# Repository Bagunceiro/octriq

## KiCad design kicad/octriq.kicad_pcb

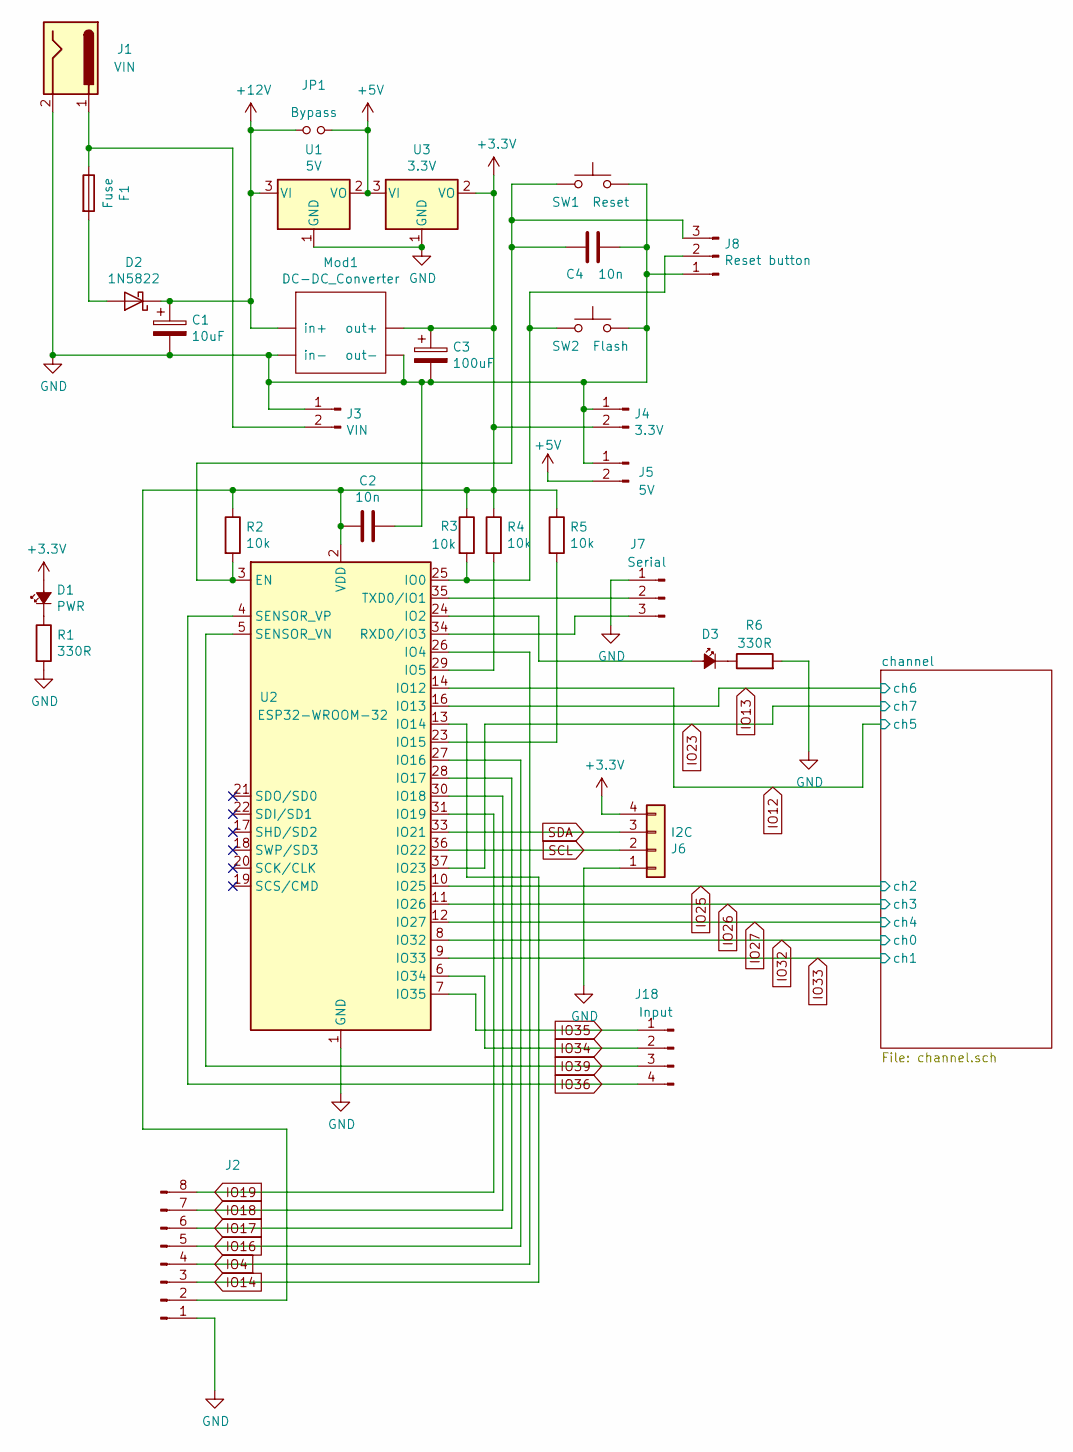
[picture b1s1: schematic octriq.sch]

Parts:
C1: 10uF; CP_Radial_D12.5mm_P7.50mm+pins
C2, C4: 10n; C_0805_2012Metric_Pad1.15x1.40mm_HandSolder
C3: 100uF; CP_Radial_D12.5mm_P7.50mm+pins
D1: PWR; LED_0805_2012Metric_Pad1.15x1.40mm_HandSolder
D2: 1N5822; D_DO-201AD_P5.08mm_Vertical_AnodeUp
D3: BUILT-IN; LED_0805_2012Metric_Pad1.15x1.40mm_HandSolder
F1: Fuse; R_Axial_DIN0411_L9.9mm_D3.6mm_P15.24mm_Horizontal
J1: VIN; BarrelJack_Horizontal
J2: Conn_01x06_Male; PinHeader_3x06_P2.54mm_Vertical
J3: VIN; PinHeader_1x02_P2.54mm_Vertical
J4: 3.3V; PinHeader_1x02_P2.54mm_Vertical
J5: 5V; PinHeader_1x02_P2.54mm_Vertical
J6: I2C; PinHeader_1x04_P2.54mm_Vertical
J7: Serial; PinHeader_1x03_P2.54mm_Vertical
J8: Reset button; PinHeader_1x03_P2.54mm_Vertical
J18: Input; PinHeader_1x04_P2.54mm_Vertical
JP1: Bypass; SolderJumper-2_P1.3mm_Open_TrianglePad1.0x1.5mm
Mod1: DC-DC_Converter; small_Buck
R1, R6: 330R; R_0805_2012Metric_Pad1.15x1.40mm_HandSolder
R2, R3, R4, R5: 10k; R_0805_2012Metric_Pad1.15x1.40mm_HandSolder
SW1: Reset; SW_PUSH_6mm
SW2: Flash; SW_PUSH_6mm
U1: 5V; SOT-223-3_TabPin2
U2: ESP32-WROOM-32
U3: 3.3V; SOT-223-3_TabPin2

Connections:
+3V3: C2.2, C3.1, D1.2 (A), J2.2, J4.2, J6.4, Mod1.2 (out+), R2.1, R3.1, R4.1, R5.1, U2.2 (VDD), U3.2 (VO)
+5V: J5.2, JP1.2, U1.2 (VO), U3.3 (VI)
+12V: C1.1, D2.1 (K), JP1.1, Mod1.1 (in+), U1.3 (VI); also elsewhere on the board
GND: C1.2, C2.1, C3.2, C4.1, J1.2, J2.1, J3.1, J4.1, J5.1, J6.1, J7.1, J8.1, Mod1.3 (out-), Mod1.4 (in-), R1.2, R6.2, SW1.2, SW2.2, U1.1 (GND), U2.1 (GND), U2.15 (GND), U2.38 (GND), U2.39 (GND), U3.1 (GND); also elsewhere on the board
IO4: J2.4, U2.26 (IO4)
IO12: U2.14 (IO12); also elsewhere on the board
IO13: U2.16 (IO13); also elsewhere on the board
IO14: J2.3, U2.13 (IO14)
IO16: J2.5, U2.27 (IO16)
IO17: J2.6, U2.28 (IO17)
IO18: J2.7, U2.30 (IO18)
IO19: J2.8, U2.31 (IO19)
IO23: U2.37 (IO23); also elsewhere on the board
IO25: U2.10 (IO25); also elsewhere on the board
IO26: U2.11 (IO26); also elsewhere on the board
IO27: U2.12 (IO27); also elsewhere on the board
IO32: U2.8 (IO32); also elsewhere on the board
IO33: U2.9 (IO33); also elsewhere on the board
IO34: J18.2, U2.6 (IO34)
IO35: J18.1, U2.7 (IO35)
IO36: J18.4, U2.4 (SENSOR_VP)
IO39: J18.3, U2.5 (SENSOR_VN)
unnamed: C4.2, J8.3, R2.2, SW1.1, U2.3 (EN)
unnamed: D1.1 (K), R1.1
unnamed: D2.2 (A), F1.2
unnamed: D3.1 (K), R6.1
unnamed: D3.2 (A), U2.24 (IO2)
unnamed: F1.1, J1.1, J3.2
unnamed: J7.2, U2.35 (TXD0/IO1)
unnamed: J7.3, U2.34 (RXD0/IO3)
unnamed: J8.2, R3.2, SW2.1, U2.25 (IO0)
unnamed: R4.2, U2.29 (IO5)
unnamed: R5.2, U2.23 (IO15)
SCL: J6.2, U2.36 (IO22)
SDA: J6.3, U2.33 (IO21)

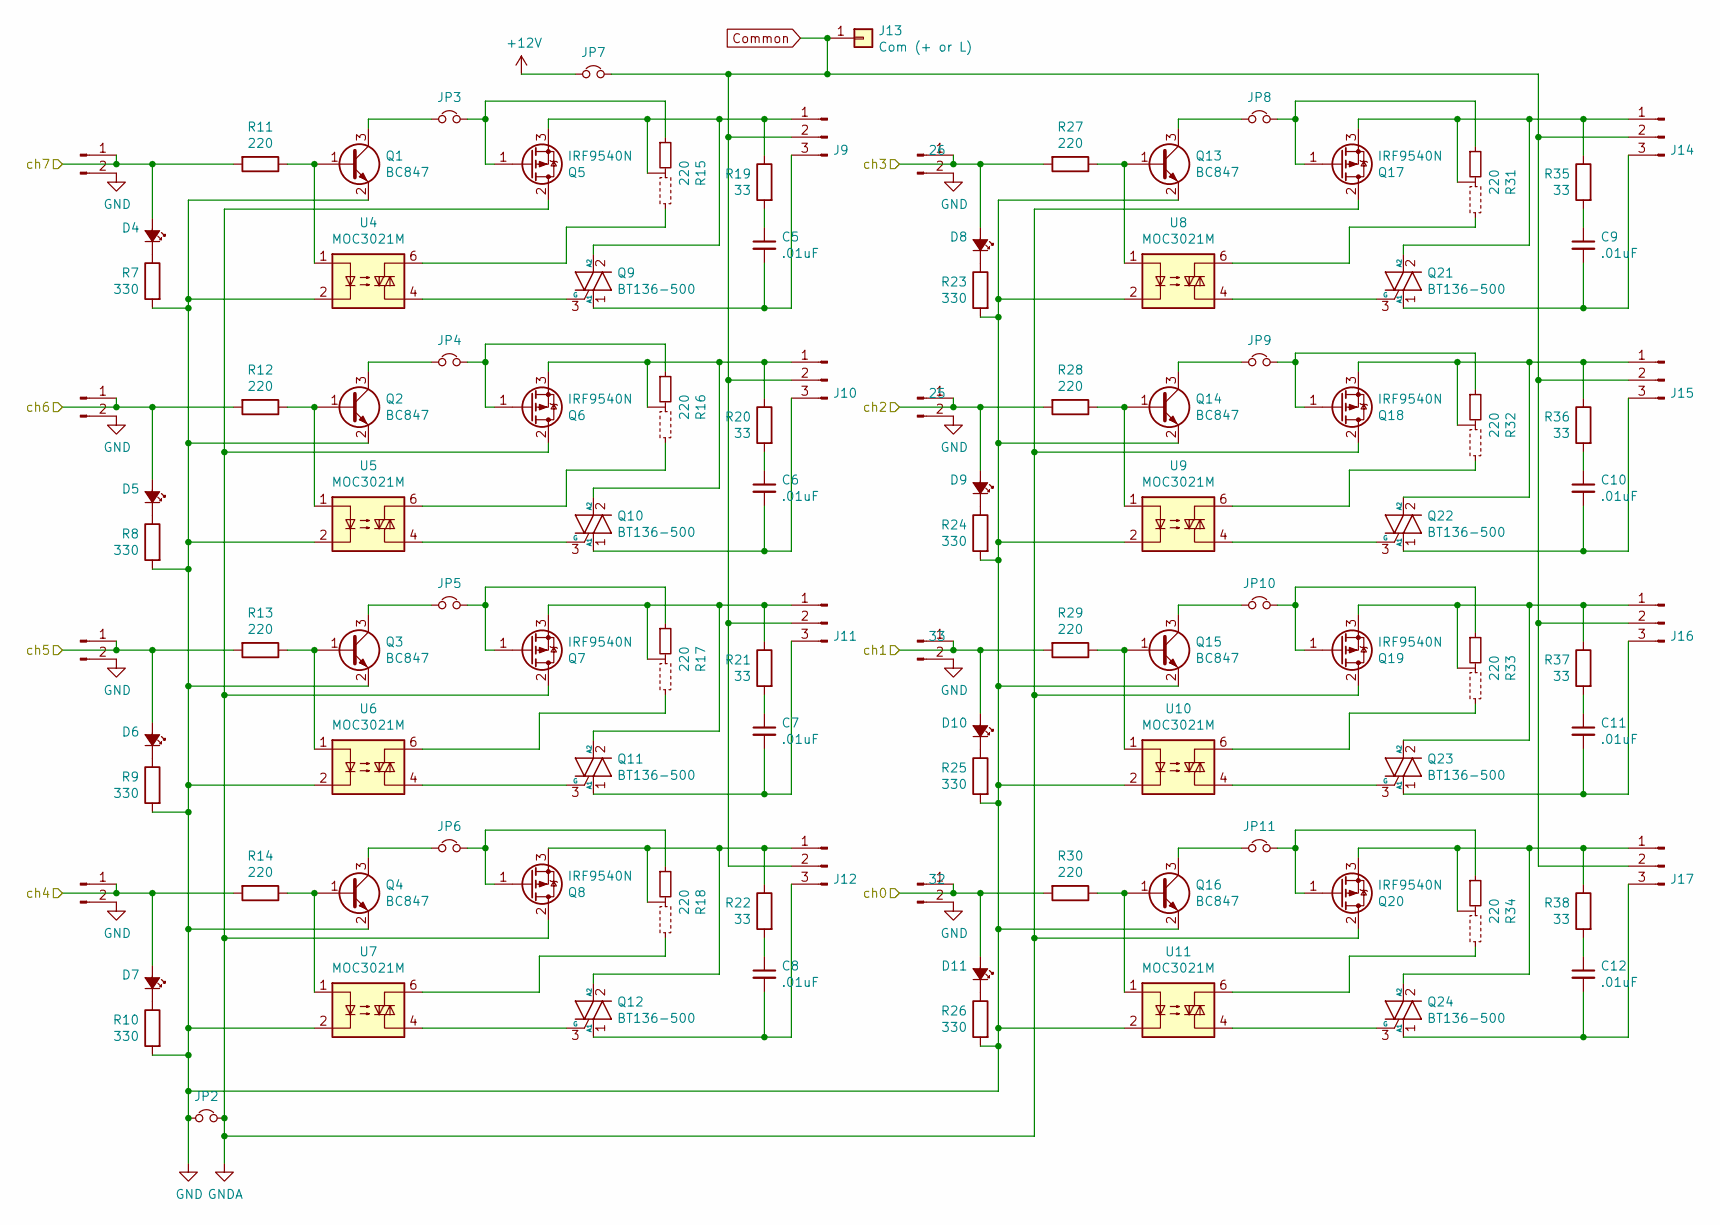
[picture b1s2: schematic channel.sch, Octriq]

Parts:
C5, C6, C7, C8, C9, C10, C11, C12: .01uF; C_0805_2012Metric_Pad1.15x1.40mm_HandSolder
D4, D5, D6, D7, D8, D9, D10, D11: LED_Small_ALT; LED_0805_2012Metric_Pad1.15x1.40mm_HandSolder
J9, J10, J11, J12, J14, J15, J16, J17: Conn_01x03_Male; Molex_KK+Born2
J13: Com (+ or L); Spade_Terminal
JP2, JP3, JP4, JP5, JP6, JP7, JP8, JP9, JP10, JP11: Jumper_NC_Small; wide_jumper
Q1, Q2, Q3, Q4, Q13, Q14, Q15, Q16: BC847; SOT-23
Q5, Q6, Q7, Q8, Q17, Q18, Q19, Q20: IRF9540N; TO-220-3_Vertical
Q9, Q10, Q11, Q12, Q21, Q22, Q23, Q24: BT136-500; TO-220-3_Vertical
R7, R8, R9, R10, R23, R24, R25, R26: 330; R_0805_2012Metric_Pad1.15x1.40mm_HandSolder
R11, R12, R13, R14, R27, R28, R29, R30: 220; R_0805_2012Metric_Pad1.15x1.40mm_HandSolder
R15, R16, R17, R18, R31, R32, R33, R34: 220; Resistor_0805_option
R19, R20, R21, R22, R35, R36, R37, R38: 33; R_0805_2012Metric_Pad1.15x1.40mm_HandSolder
TP1: 13; PinHeader_1x02_P2.54mm_Vertical
TP2: 12; PinHeader_1x02_P2.54mm_Vertical
TP3: 14; PinHeader_1x02_P2.54mm_Vertical
TP4: 27; PinHeader_1x02_P2.54mm_Vertical
TP5: 26; PinHeader_1x02_P2.54mm_Vertical
TP6: 25; PinHeader_1x02_P2.54mm_Vertical
TP7: 33; PinHeader_1x02_P2.54mm_Vertical
TP8: 32; PinHeader_1x02_P2.54mm_Vertical
U4, U5, U6, U7, U8, U9, U10, U11: MOC3021M; DIP-6_W7.62mm_Socket

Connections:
+12V: JP7.1; also elsewhere on the board
Common: J9.2, J10.2, J11.2, J12.2, J13.1, J14.2, J15.2, J16.2, J17.2, JP7.2
GND: JP2.1, Q1.2 (E), Q2.2 (E), Q3.2 (E), Q4.2 (E), Q13.2 (E), Q14.2 (E), Q15.2 (E), Q16.2 (E), R7.2, R8.2, R9.2, R10.2, R23.2, R24.2, R25.2, R26.2, TP1.2, TP2.2, TP3.2, TP4.2, TP5.2, TP6.2, TP7.2, TP8.2, U4.2, U5.2, U6.2, U7.2, U8.2, U9.2, U10.2, U11.2; also elsewhere on the board
GNDA: JP2.2, Q5.2 (D), Q6.2 (D), Q7.2 (D), Q8.2 (D), Q17.2 (D), Q18.2 (D), Q19.2 (D), Q20.2 (D)
IO12: D6.2 (A), R13.2, TP3.1; also elsewhere on the board
IO13: D5.2 (A), R12.2, TP2.1; also elsewhere on the board
IO23: D4.2 (A), R11.2, TP1.1; also elsewhere on the board
IO25: D9.2 (A), R28.2, TP6.1; also elsewhere on the board
IO26: D8.2 (A), R27.2, TP5.1; also elsewhere on the board
IO27: D7.2 (A), R14.2, TP4.1; also elsewhere on the board
IO32: D11.2 (A), R30.2, TP8.1; also elsewhere on the board
IO33: D10.2 (A), R29.2, TP7.1; also elsewhere on the board
unnamed: C5.1, R19.2
unnamed: C5.2, J9.3, Q9.1 (A1)
unnamed: C6.1, R20.2
unnamed: C6.2, J10.3, Q10.1 (A1)
unnamed: C7.1, R21.2
unnamed: C7.2, J11.3, Q11.1 (A1)
unnamed: C8.1, R22.2
unnamed: C8.2, J12.3, Q12.1 (A1)
unnamed: C9.1, R35.2
unnamed: C9.2, J14.3, Q21.1 (A1)
unnamed: C10.1, R36.2
unnamed: C10.2, J15.3, Q22.1 (A1)
unnamed: C11.1, R37.2
unnamed: C11.2, J16.3, Q23.1 (A1)
unnamed: C12.1, R38.2
unnamed: C12.2, J17.3, Q24.1 (A1)
unnamed: D4.1 (K), R7.1
unnamed: D5.1 (K), R8.1
unnamed: D6.1 (K), R9.1
unnamed: D7.1 (K), R10.1
unnamed: D8.1 (K), R23.1
unnamed: D9.1 (K), R24.1
unnamed: D10.1 (K), R25.1
unnamed: D11.1 (K), R26.1
unnamed: J9.1, Q5.3 (S), Q9.2 (A2), R15.1 (Common), R19.1
unnamed: J10.1, Q6.3 (S), Q10.2 (A2), R16.1 (Common), R20.1
unnamed: J11.1, Q7.3 (S), Q11.2 (A2), R17.1 (Common), R21.1
unnamed: J12.1, Q8.3 (S), Q12.2 (A2), R18.1 (Common), R22.1
unnamed: J14.1, Q17.3 (S), Q21.2 (A2), R31.1 (Common), R35.1
unnamed: J15.1, Q18.3 (S), Q22.2 (A2), R32.1 (Common), R36.1
unnamed: J16.1, Q19.3 (S), Q23.2 (A2), R33.1 (Common), R37.1
unnamed: J17.1, Q20.3 (S), Q24.2 (A2), R34.1 (Common), R38.1
unnamed: JP3.1, Q1.3 (C)
unnamed: JP3.2, Q5.1 (G), R15.2
unnamed: JP4.1, Q2.3 (C)
unnamed: JP4.2, Q6.1 (G), R16.2
unnamed: JP5.1, Q3.3 (C)
unnamed: JP5.2, Q7.1 (G), R17.2
unnamed: JP6.1, Q4.3 (C)
unnamed: JP6.2, Q8.1 (G), R18.2
unnamed: JP8.1, Q13.3 (C)
unnamed: JP8.2, Q17.1 (G), R31.2
unnamed: JP9.1, Q14.3 (C)
unnamed: JP9.2, Q18.1 (G), R32.2
unnamed: JP10.1, Q15.3 (C)
unnamed: JP10.2, Q19.1 (G), R33.2
unnamed: JP11.1, Q16.3 (C)
unnamed: JP11.2, Q20.1 (G), R34.2
unnamed: Q1.1 (B), R11.1, U4.1
unnamed: Q2.1 (B), R12.1, U5.1
unnamed: Q3.1 (B), R13.1, U6.1
unnamed: Q4.1 (B), R14.1, U7.1
unnamed: Q9.3 (G), U4.4
unnamed: Q10.3 (G), U5.4
unnamed: Q11.3 (G), U6.4
unnamed: Q12.3 (G), U7.4
unnamed: Q13.1 (B), R27.1, U8.1
unnamed: Q14.1 (B), R28.1, U9.1
unnamed: Q15.1 (B), R29.1, U10.1
unnamed: Q16.1 (B), R30.1, U11.1
unnamed: Q21.3 (G), U8.4
unnamed: Q22.3 (G), U9.4
unnamed: Q23.3 (G), U10.4
unnamed: Q24.3 (G), U11.4
unnamed: R15.3, U4.6
unnamed: R16.3, U5.6
unnamed: R17.3, U6.6
unnamed: R18.3, U7.6
unnamed: R31.3, U8.6
unnamed: R32.3, U9.6
unnamed: R33.3, U10.6
unnamed: R34.3, U11.6

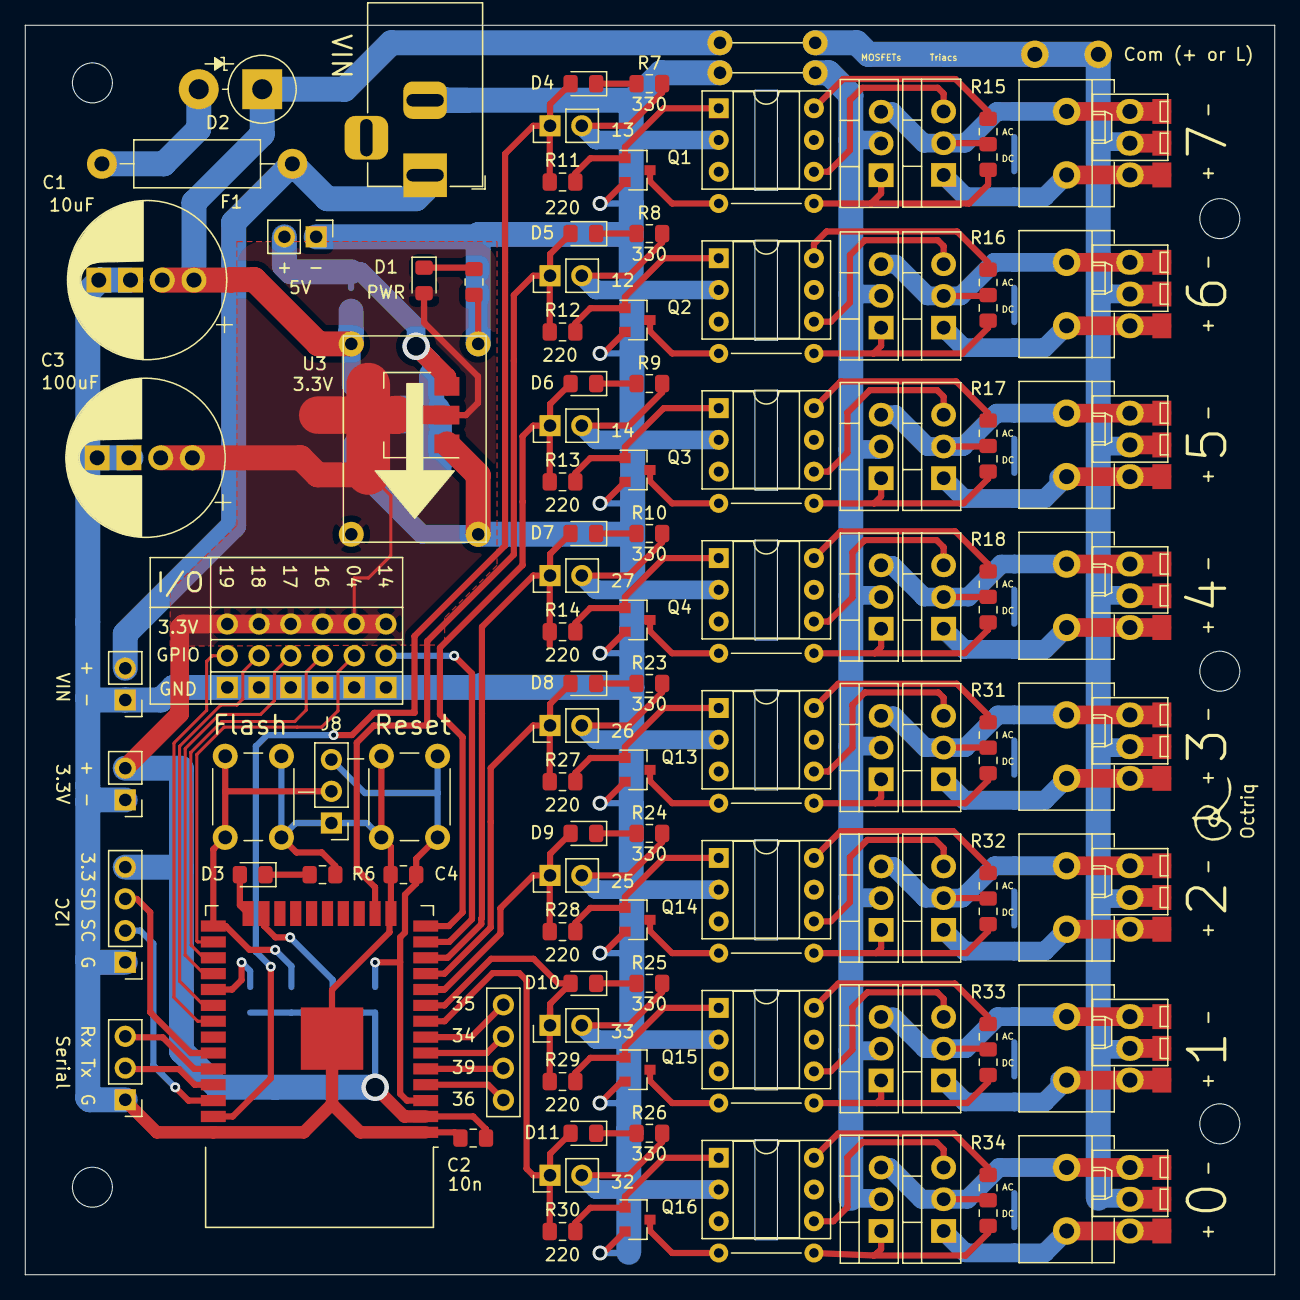
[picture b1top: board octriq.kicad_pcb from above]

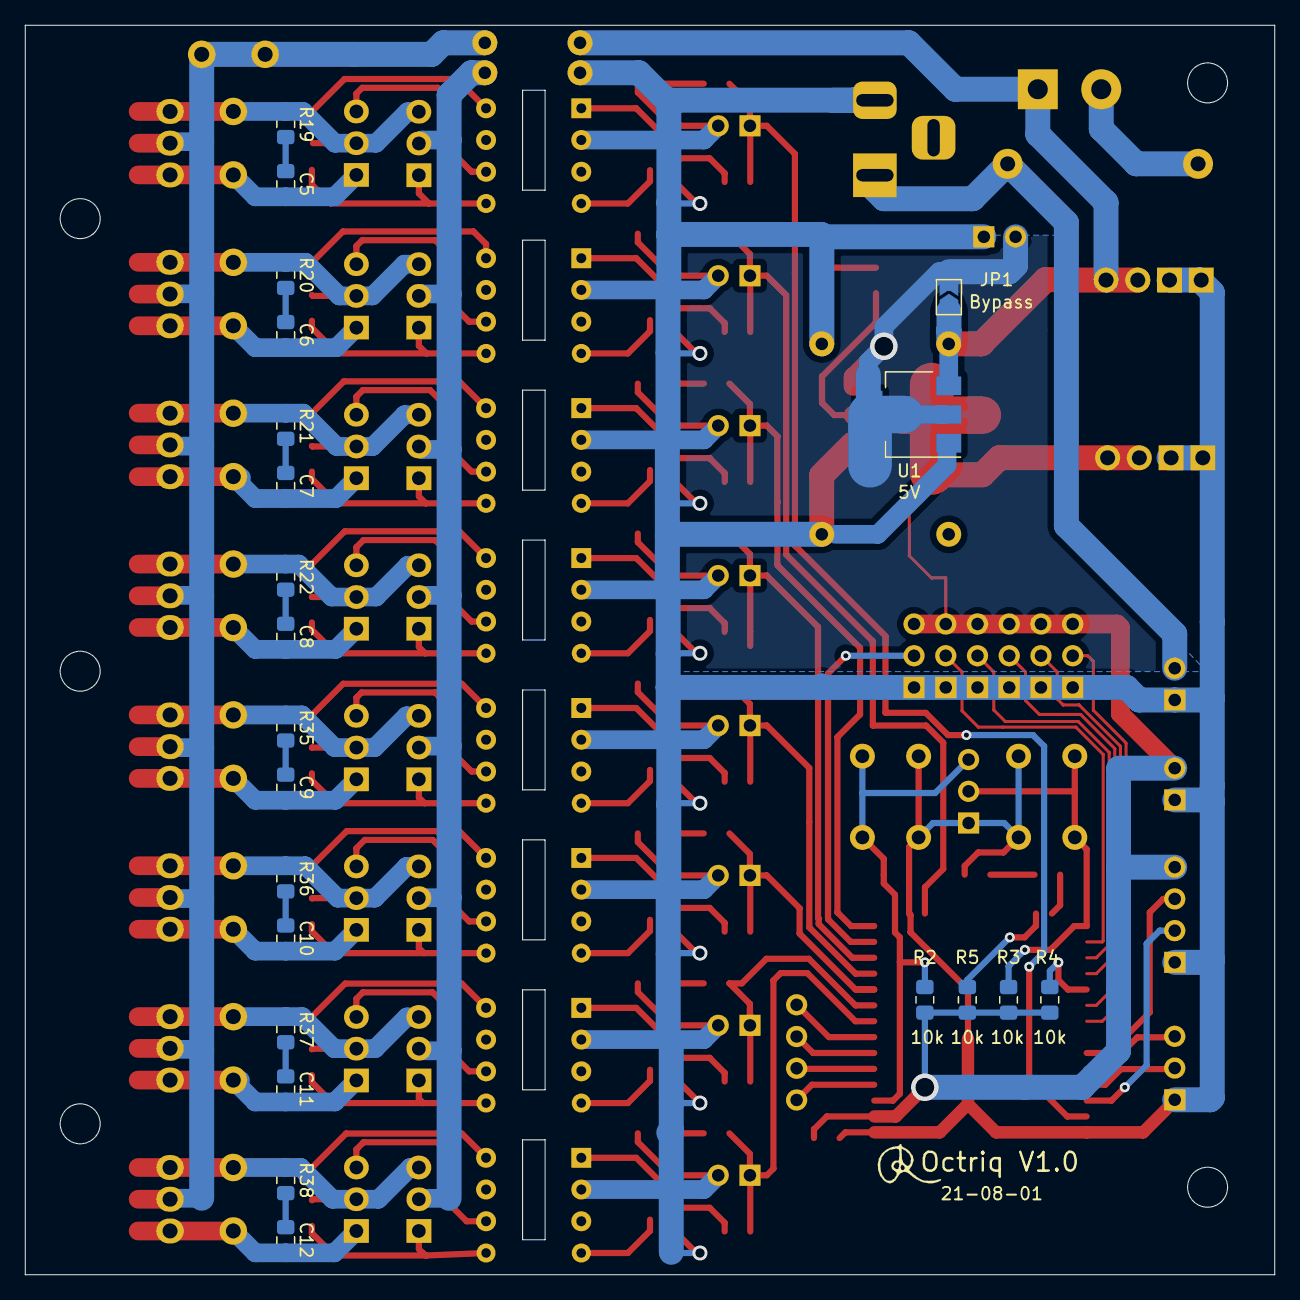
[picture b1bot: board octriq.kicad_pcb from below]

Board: 2 copper layers, 100.0 x 100.0 mm, 137 parts (22 on the bottom side), 109 nets.

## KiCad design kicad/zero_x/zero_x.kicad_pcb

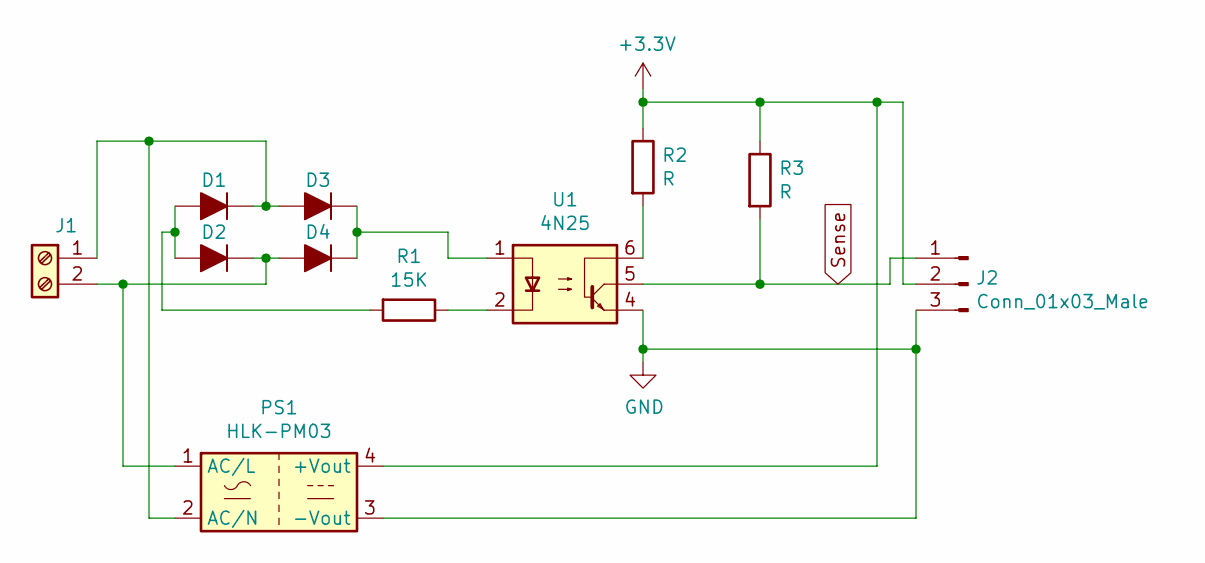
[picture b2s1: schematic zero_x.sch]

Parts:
D1, D2, D3, D4: D_ALT; D_A-405_P7.62mm_Horizontal
J1: Screw_Terminal_01x02; TerminalBlock_bornier-2_P5.08mm
J2: Conn_01x03_Male; PinHeader_1x03_P2.54mm_Vertical
PS1: HLK-PM03; Converter_ACDC_HiLink_HLK-PMxx
R1: 15K; R_Axial_DIN0617_L17.0mm_D6.0mm_P7.62mm_Vertical
R2, R3: R; R_Axial_DIN0207_L6.3mm_D2.5mm_P7.62mm_Horizontal
U1: 4N25; DIP-6_W7.62mm

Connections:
+3V3: J2.2, PS1.4 (+Vout), R2.1, R3.1
GND: J2.3, PS1.3 (-Vout), U1.4
unnamed: D1.1 (K), D3.2 (A), J1.1, PS1.2 (AC/N)
unnamed: D1.2 (A), D2.2 (A), R1.2
unnamed: D2.1 (K), D4.2 (A), J1.2, PS1.1 (AC/L)
unnamed: D3.1 (K), D4.1 (K), U1.1
unnamed: R1.1, U1.2
unnamed: R2.2, U1.6
Sense: J2.1, R3.2, U1.5

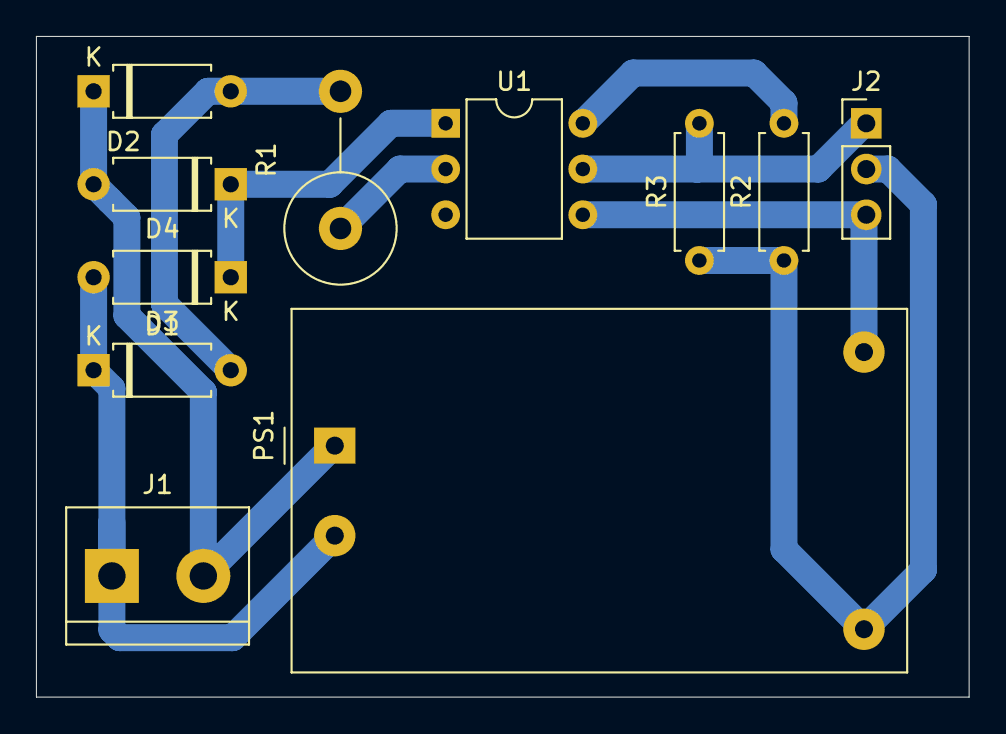
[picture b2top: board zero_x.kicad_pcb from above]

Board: 2 copper layers, 51.8 x 36.7 mm, 11 parts (0 on the bottom side), 9 nets.

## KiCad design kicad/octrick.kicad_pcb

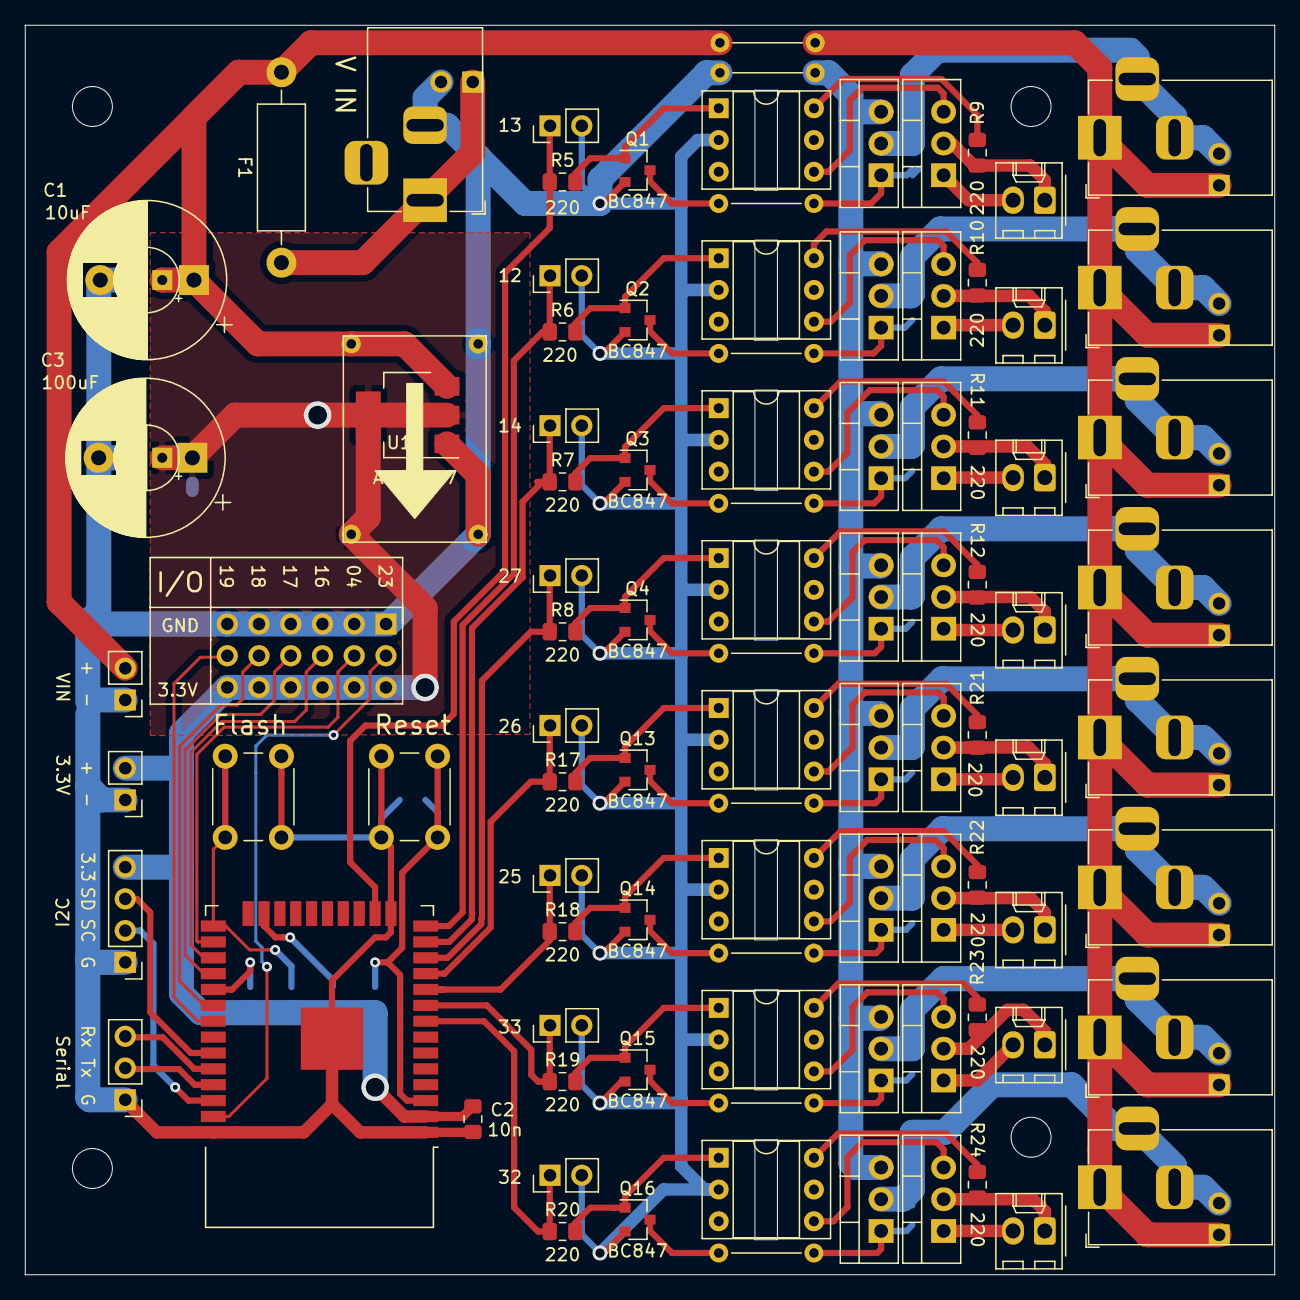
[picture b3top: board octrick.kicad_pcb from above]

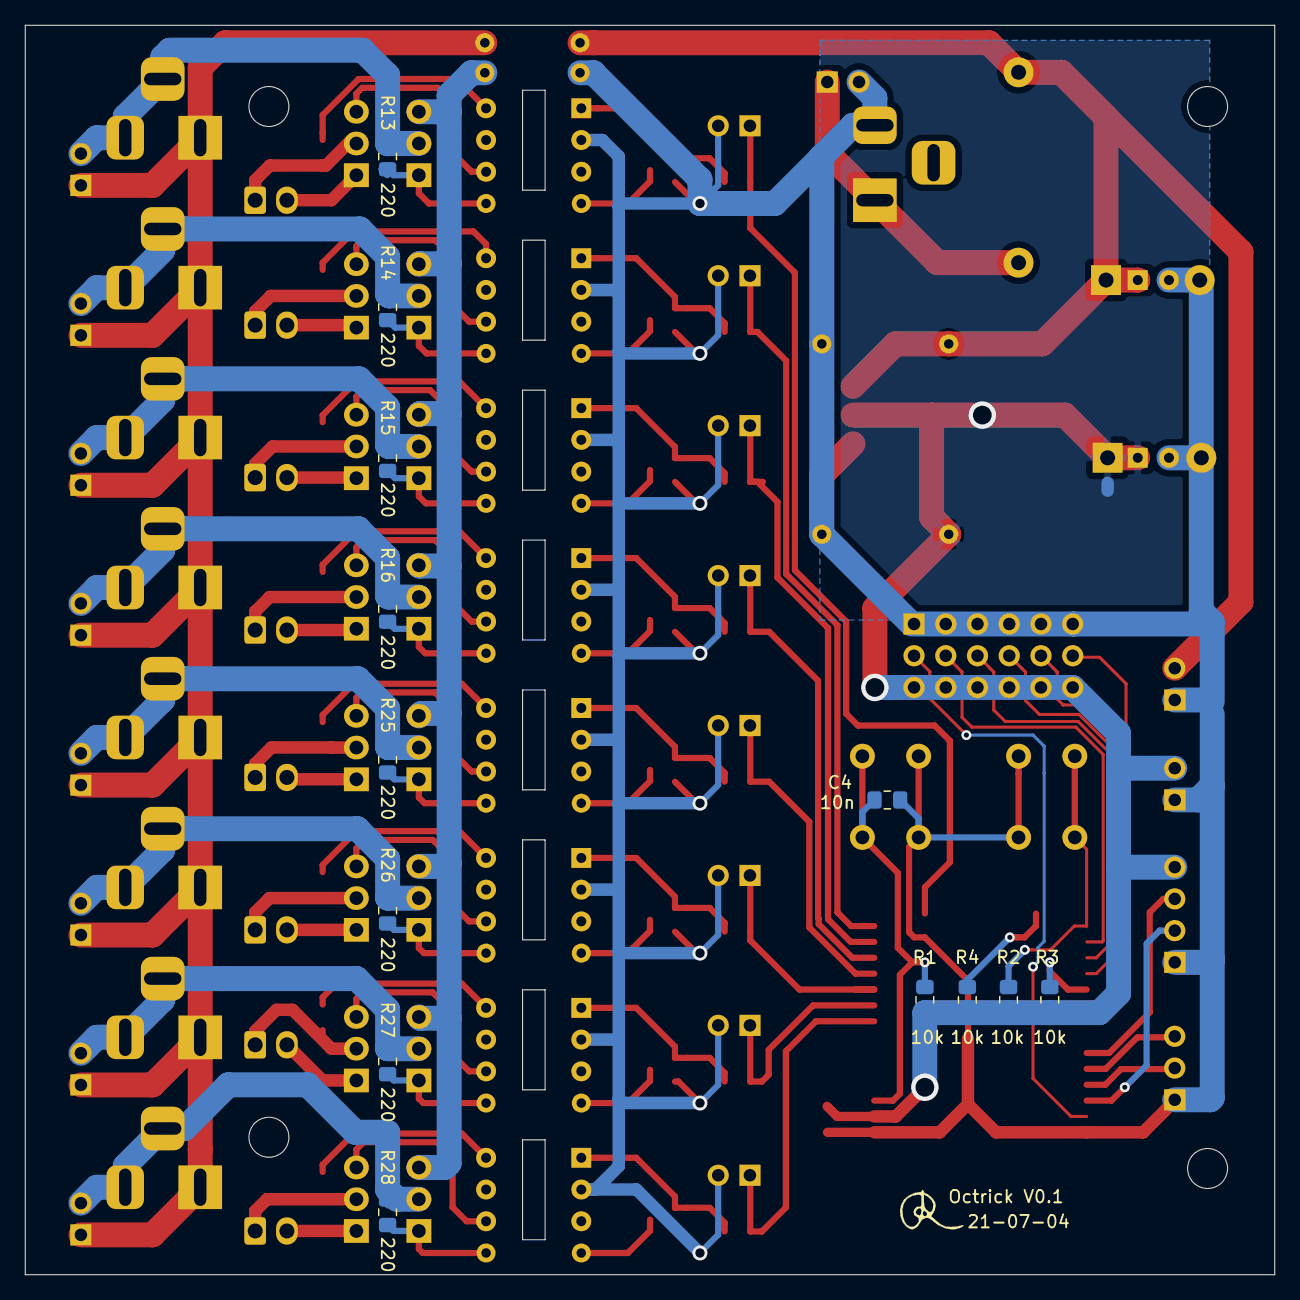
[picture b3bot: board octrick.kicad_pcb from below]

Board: 2 copper layers, 100.0 x 100.0 mm, 110 parts (13 on the bottom side), 92 nets.

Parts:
C1: 10uF; CP_Radial_D12.5mm_P7.50mm
C2, C4: 10n; C_0805_2012Metric_Pad1.15x1.40mm_HandSolder
C3: 100uF; CP_Radial_D12.5mm_P7.50mm
F1: Fuse; R_Axial_DIN0411_L9.9mm_D3.6mm_P15.24mm_Horizontal
J1: V IN; BarrelJack_Horizontal
J2: Conn_01x06_Male; PinHeader_3x06_P2.54mm_Vertical
J3: VIN; PinHeader_1x02_P2.54mm_Vertical
J4: 3.3V; PinHeader_1x02_P2.54mm_Vertical
J5: Serial; PinHeader_1x03_P2.54mm_Vertical
J6: I2C; PinHeader_1x04_P2.54mm_Vertical
J7, J8, J9, J10, J15, J16, J17, J18: Barrel_Jack_Switch; BarrelJack_Horizontal
J11, J12, J13, J14, J19, J20, J21, J22: Conn_01x02_Male; Molex_KK-254_AE-6410-02A_1x02_P2.54mm_Vertical
JP1, JP2, JP3, JP4, JP5, JP6, JP7, JP8, JP9, JP10: Jumper_NC_Small; wide_jumper
Mod1: DC-DC_Converter; small_Buck
Q1, Q2, Q3, Q4, Q13, Q14, Q15, Q16: BC847; SOT-23
Q5, Q6, Q7, Q8, Q17, Q18, Q19, Q20: IRF9540N; TO-220-3_Vertical
Q9, Q10, Q11, Q12, Q21, Q22, Q23, Q24: BT136-500; TO-220-3_Vertical
R1, R2, R3, R4: 10k; R_0805_2012Metric_Pad1.15x1.40mm_HandSolder
R5, R6, R7, R8, R9, R10, R11, R12, R13, R14, R15, R16, R17, R18, R19, R20, R21, R22, R23, R24, R25, R26, R27, R28: 220; R_0805_2012Metric_Pad1.15x1.40mm_HandSolder
SW1: Reset; SW_PUSH_6mm
SW2: Flash; SW_PUSH_6mm
TP1: 13; PinHeader_1x02_P2.54mm_Vertical
TP2: 12; PinHeader_1x02_P2.54mm_Vertical
TP3: 14; PinHeader_1x02_P2.54mm_Vertical
TP4: 27; PinHeader_1x02_P2.54mm_Vertical
TP5: 26; PinHeader_1x02_P2.54mm_Vertical
TP6: 25; PinHeader_1x02_P2.54mm_Vertical
TP7: 33; PinHeader_1x02_P2.54mm_Vertical
TP8: 32; PinHeader_1x02_P2.54mm_Vertical
U1: ESP32-WROOM-32
U2, U3, U4, U5, U6, U7, U8, U9: MOC3021M; DIP-6_W7.62mm_Socket
U10: AMS1117; SOT-223-3_TabPin2

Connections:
+3V3: C2.2, C3.1, J2.2, J4.2, J6.4, Mod1.2, R1.1, R2.1, R3.1, R4.1, U1.2, U10.2
+12V: C1.1, F1.2, J3.2, JP6.1, Mod1.1, U10.3
+12VA: J7.1, J8.1, J9.1, J10.1, J15.1, J16.1, J17.1, J18.1, JP6.2
GND: C1.2, C2.1, C3.2, C4.1, J1.2, J2.1, J3.1, J4.1, J5.1, J6.1, JP1.1, Mod1.3, Mod1.4, Q1.2, Q2.2, Q3.2, Q4.2, Q13.2, Q14.2, Q15.2, Q16.2, SW1.2, SW2.2, TP1.2, TP2.2, TP3.2, TP4.2, TP5.2, TP6.2, TP7.2, TP8.2, U1.1, U1.15, U1.38, U1.39, U2.2, U3.2, U4.2, U5.2, U6.2, U7.2, U8.2, U9.2, U10.1
GNDA: JP1.2, Q5.3, Q6.3, Q7.3, Q8.3, Q17.3, Q18.3, Q19.3, Q20.3
IO4: J2.4, U1.26
IO12: R6.2, TP2.1, U1.14
IO13: R5.2, TP1.1, U1.16
IO14: R7.2, TP3.1, U1.13
IO16: J2.5, U1.27
IO17: J2.6, U1.28
IO18: J2.7, U1.30
IO19: J2.8, U1.31
IO23: J2.3, U1.37
IO25: R18.2, TP6.1, U1.10
IO26: R17.2, TP5.1, U1.11
IO27: R8.2, TP4.1, U1.12
IO32: R20.2, TP8.1, U1.8
IO33: R19.2, TP7.1, U1.9
unnamed: C4.2, R1.2, SW1.1, U1.3
unnamed: F1.1, J1.1
unnamed: J5.2, U1.35
unnamed: J5.3, U1.34
unnamed: J7.2, J7.3, Q5.2, R13.1
unnamed: J8.2, J8.3, Q6.2, R14.1
unnamed: J9.2, J9.3, Q7.2, R15.1
unnamed: J10.2, J10.3, Q8.2, R16.1
unnamed: J11.1, Q9.2, R9.1
unnamed: J11.2, Q9.1
unnamed: J12.1, Q10.2, R10.1
unnamed: J12.2, Q10.1
unnamed: J13.1, Q11.2, R11.1
unnamed: J13.2, Q11.1
unnamed: J14.1, Q12.2, R12.1
unnamed: J14.2, Q12.1
unnamed: J15.2, J15.3, Q17.2, R25.1
unnamed: J16.2, J16.3, Q18.2, R26.1
unnamed: J17.2, J17.3, Q19.2, R27.1
unnamed: J18.2, J18.3, Q20.2, R28.1
unnamed: J19.1, Q21.2, R21.1
unnamed: J19.2, Q21.1
unnamed: J20.1, Q22.2, R22.1
unnamed: J20.2, Q22.1
unnamed: J21.1, Q23.2, R23.1
unnamed: J21.2, Q23.1
unnamed: J22.1, Q24.2, R24.1
unnamed: J22.2, Q24.1
unnamed: JP2.1, Q1.3
unnamed: JP2.2, Q5.1, R13.2
unnamed: JP3.1, Q2.3
unnamed: JP3.2, Q6.1, R14.2
unnamed: JP4.1, Q3.3
unnamed: JP4.2, Q7.1, R15.2
unnamed: JP5.1, Q4.3
unnamed: JP5.2, Q8.1, R16.2
unnamed: JP7.1, Q13.3
unnamed: JP7.2, Q17.1, R25.2
unnamed: JP8.1, Q14.3
unnamed: JP8.2, Q18.1, R26.2
unnamed: JP9.1, Q15.3
unnamed: JP9.2, Q19.1, R27.2
unnamed: JP10.1, Q16.3
unnamed: JP10.2, Q20.1, R28.2
unnamed: Q1.1, R5.1, U2.1
unnamed: Q2.1, R6.1, U3.1
unnamed: Q3.1, R7.1, U4.1
unnamed: Q4.1, R8.1, U5.1
unnamed: Q9.3, U2.4
unnamed: Q10.3, U3.4
unnamed: Q11.3, U4.4
unnamed: Q12.3, U5.4
unnamed: Q13.1, R17.1, U6.1
unnamed: Q14.1, R18.1, U7.1
unnamed: Q15.1, R19.1, U8.1
unnamed: Q16.1, R20.1, U9.1
unnamed: Q21.3, U6.4
unnamed: Q22.3, U7.4
unnamed: Q23.3, U8.4
unnamed: Q24.3, U9.4
unnamed: R2.2, SW2.1, U1.25
unnamed: R3.2, U1.29
unnamed: R4.2, U1.23
unnamed: R9.2, U2.6
unnamed: R10.2, U3.6
unnamed: R11.2, U4.6
unnamed: R12.2, U5.6
unnamed: R21.2, U6.6
unnamed: R22.2, U7.6
unnamed: R23.2, U8.6
unnamed: R24.2, U9.6
SCL: J6.2, U1.36
SDA: J6.3, U1.33

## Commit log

2021-07-05 Kicad files as sent for manufacture
2021-07-16 added VM as library
2021-07-16 Incorporate Utils
2021-07-16 Add language header into make dependencies
2021-07-17 VM working on ESP
2021-07-17 Add hardware
2021-07-17 run from memory
2021-07-18 Implemented RUN instruction
2021-07-18 various
2021-07-19 Indirection
2021-07-20 Exponential mapping for channel set
2021-07-20 HWM monitoring
2021-07-22 Minor fixes
2021-07-22 checkpoint
2021-07-23 Remove timecode - replace with dly op
2021-07-23 Tidier
2021-08-01 V1.0 board as ordered
